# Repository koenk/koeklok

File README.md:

# Koeklok

Firmware, schematics and PCBs for Koeklok, a small modular clock.

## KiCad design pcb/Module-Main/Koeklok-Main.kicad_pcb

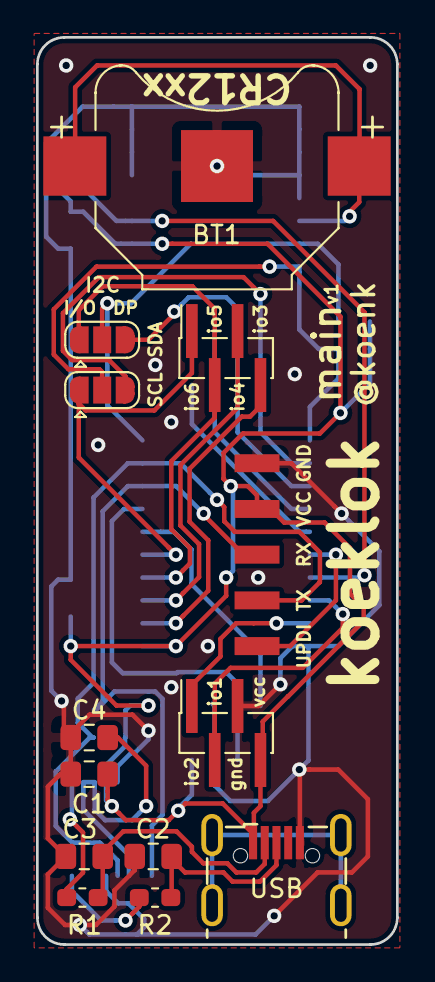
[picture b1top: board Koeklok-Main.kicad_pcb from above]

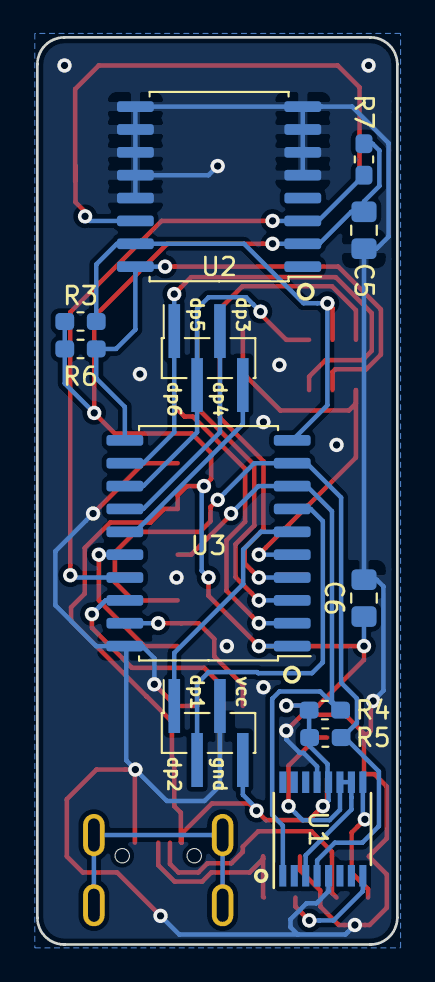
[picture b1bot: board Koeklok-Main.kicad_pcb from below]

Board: 2 copper layers, 20.0 x 50.4 mm, 25 parts (12 on the bottom side), 26 nets.

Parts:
BT1: Battery_Cell; BatteryHolder_Keystone_3000_1x12mm
C1: 10nF; C_0805_2012Metric_Pad1.15x1.40mm_HandSolder
C2, C3: 47pF; C_0805_2012Metric_Pad1.15x1.40mm_HandSolder
C4: 100nF; C_0805_2012Metric_Pad1.15x1.40mm_HandSolder
C5: 100pF; C_0805_2012Metric_Pad1.15x1.40mm_HandSolder
C6: 100uF; C_0805_2012Metric_Pad1.15x1.40mm_HandSolder
J1: USB; USB_Micro-B_4DIP
J2: Debug pins; Harwin_M20-89005xx_1x05_P2.54mm_Horizontal
J3: CONN_DISP_1; PinHeader_1x04_P1.27mm_Vertical_SMD_Pin1Right
J4: CONN_DISP_2; PinHeader_1x04_P1.27mm_Vertical_SMD_Pin1Right
J5: CONN_IO_1; PinHeader_1x04_P1.27mm_Vertical_SMD_Pin1Right
J6: CONN_IO_2; PinHeader_1x04_P1.27mm_Vertical_SMD_Pin1Right
JP5, JP6: SolderJumper_3_Open; SolderJumper-3_P1.3mm_Open_RoundedPad1.0x1.5mm
R1, R2: 27; R_0603_1608Metric_Pad1.05x0.95mm_HandSolder
R3, R6, R7: 4k7; R_0603_1608Metric_Pad1.05x0.95mm_HandSolder
R4, R5: 10k; R_0603_1608Metric_Pad1.05x0.95mm_HandSolder
U1: FT230XS; SSOP-16_3.9x4.9mm_P0.635mm
U2: DS3231M; SOIC-16W_7.5x10.3mm_P1.27mm
U3: ATtiny3216-S; SOIC-20W_7.5x12.8mm_P1.27mm

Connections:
+3V3: C4.1, U1.3, U1.10, U1.11
/D+: C2.1, J1.3, R2.2
/D-: C3.1, J1.2, R1.2
/DM: R1.1, U1.9
/DP: R2.1, U1.8
/Vbat: BT1.1, U2.14
GND: BT1.2, C1.2, C2.2, C3.2, C4.2, C5.1, C6.2, J1.5, J2.5, J3.3, J5.3, U1.5, U1.13, U2.5, U2.6, U2.7, U2.8, U2.9, U2.10, U2.11, U2.12, U2.13, U3.20
HDR_DISP_1: J3.2, U3.7
HDR_DISP_2: J3.1, U3.6
HDR_DISP_3: J4.4, U3.15
HDR_DISP_4: J4.3, U3.14
HDR_DISP_5: J4.2, JP5.3, U3.13
HDR_DISP_6: J4.1, JP6.3, U3.12
HDR_IO_1: J5.2, U3.18
HDR_IO_2: J5.1, U3.19
HDR_IO_3: J6.4, U3.2
HDR_IO_4: J6.3, U3.3
HDR_IO_5: J6.2, JP5.1, U3.4
HDR_IO_6: J6.1, JP6.1, U3.5
I2C_SCL: JP6.2, R6.2, U2.16, U3.11
I2C_SDA: JP5.2, R3.2, U2.15, U3.10
MCU_UART_RXD: J2.3, R4.2, U1.1, U3.8
MCU_UART_TXD: J2.2, R5.2, U1.4, U3.9
RTC_INT: R7.2, U2.3, U3.17
UPDI: J2.1, U3.16
VCC: C1.1, C5.2, C6.1, J1.1, J2.4, J3.4, J5.4, R3.1, R4.1, R5.1, R6.1, R7.1, U1.12, U2.2, U3.1

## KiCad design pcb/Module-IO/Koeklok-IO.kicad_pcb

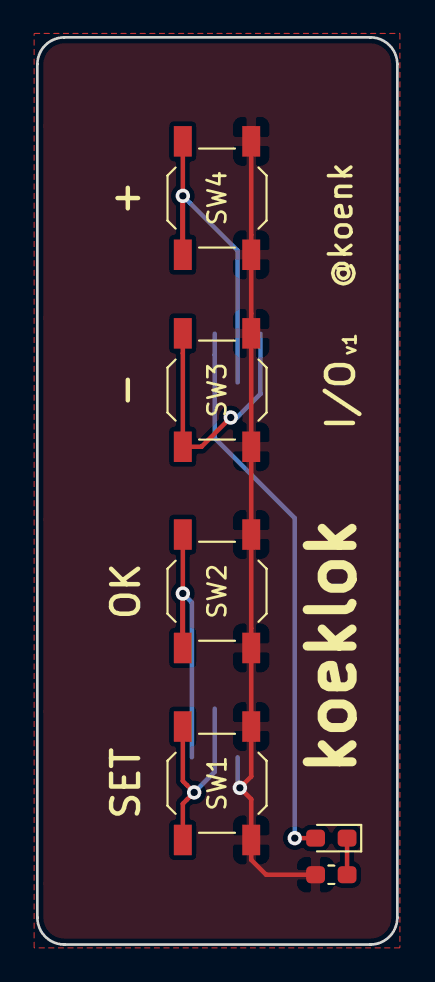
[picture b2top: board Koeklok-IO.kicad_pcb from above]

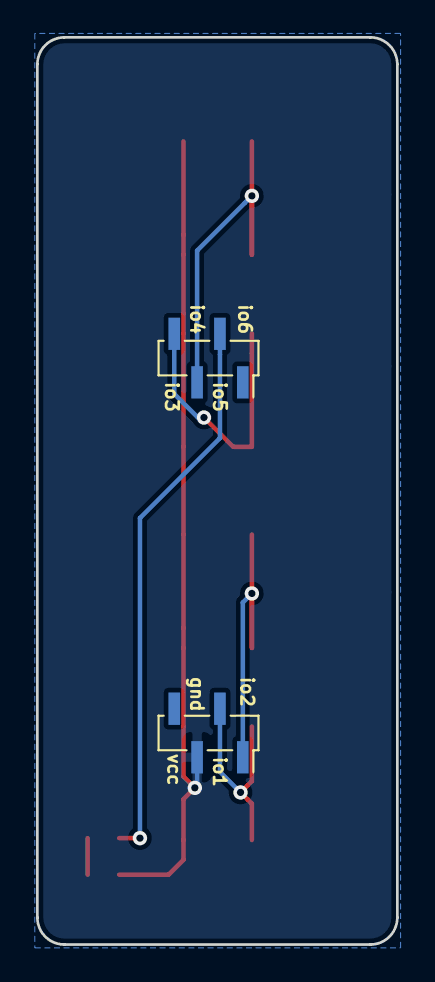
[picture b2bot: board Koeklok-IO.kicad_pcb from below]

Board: 2 copper layers, 20.0 x 50.4 mm, 8 parts (2 on the bottom side), 7 nets.

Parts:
D1: Grn; LED_0603_1608Metric_Pad1.05x0.95mm_HandSolder
J1: CONN_IO_1; PinSocket_1x04_P1.27mm_Vertical_SMD_Pin1Right
J2: CONN_IO_2; PinSocket_1x04_P1.27mm_Vertical_SMD_Pin1Right
R5: 620; R_0603_1608Metric_Pad1.05x0.95mm_HandSolder
SW1, SW2, SW3, SW4: SW_Push; SW_SPST_TL3342

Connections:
BTN1: J1.2, SW1.1
BTN2: J1.1, SW2.1
BTN3: J2.4, SW3.1
BTN4: J2.3, SW4.1
GND: J1.3, R5.1, SW1.2, SW2.2, SW3.2, SW4.2
HDR_IO_5: D1.2, J2.2
unnamed: D1.1, R5.2

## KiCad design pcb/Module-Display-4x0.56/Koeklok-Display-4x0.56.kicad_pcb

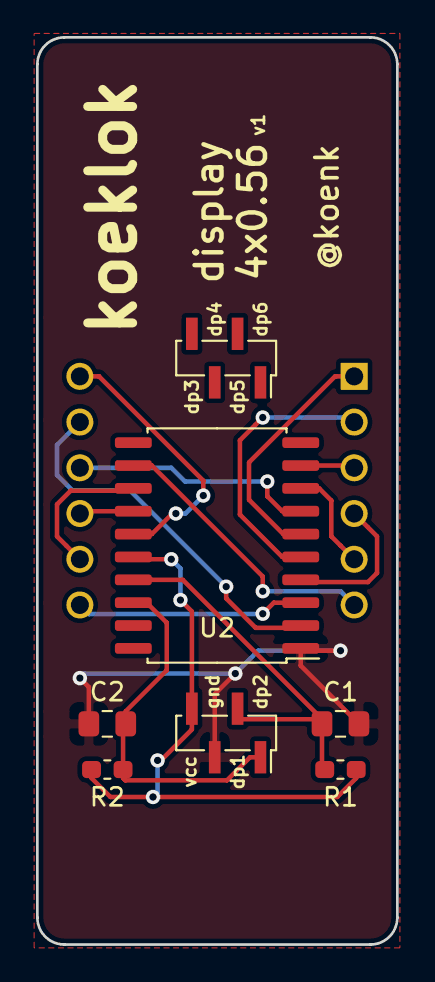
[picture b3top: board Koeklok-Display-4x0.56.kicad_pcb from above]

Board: 2 copper layers, 20.0 x 50.4 mm, 8 parts (1 on the bottom side), 16 nets.

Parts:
C1, C2: 100pF; C_0805_2012Metric_Pad1.15x1.40mm_HandSolder
J1: CONN_DISP_1; PinSocket_1x04_P1.27mm_Vertical_SMD_Pin1Right
J2: CONN_DISP_2; PinSocket_1x04_P1.27mm_Vertical_SMD_Pin1Right
R1, R2: 10k; R_0603_1608Metric_Pad1.05x0.95mm_HandSolder
U1: CA56-12EWA
U2: TM1637; SOIC-20W_7.5x12.8mm_P1.27mm

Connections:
GND: C1.2, C2.2, J1.3, U2.1
GRID1: U1.12, U2.15
GRID2: U1.9, U2.14
GRID3: U1.8, U2.13
GRID4: U1.6, U2.12
HDR_DISP_1: C1.1, J1.2, R1.2, U2.17
HDR_DISP_2: C2.1, J1.1, R2.2, U2.18
SEG1: U1.11, U2.2
SEG2: U1.7, U2.3
SEG3: U1.4, U2.4
SEG4: U1.2, U2.5
SEG5: U1.1, U2.6
SEG6: U1.10, U2.7
SEG7: U1.5, U2.8
SEG8: U1.3, U2.9
VCC: J1.4, R1.1, R2.1, U2.16

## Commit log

2019-07-09 Schema and PCB for main module
2019-07-10 Schematic for I/O module
2019-07-10 Add schematics for display modules
2020-01-26 Add USB-UART to main module, reroute main PCB.
2020-01-26 Add PCB for IO module.
2020-01-26 Add PCB for the display module (4x0.56).
2020-01-28 Minor improvements to main PCB
2020-10-25 Base bootloader, firmware and host control script. This setup allows for flashing the MCU through UART/USB via the bootloader.
